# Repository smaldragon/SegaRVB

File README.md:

# Sega R.V.B. Clone Board

This is a clone of the "Adapteur R.V.B.", used by the french market Master System II for video output, based on the schematics avaliable at [SMSPower.org](https://www.smspower.org/Development/AdapteurRVB).

This board is intended to be a cheap diy option for consoles which have lost their original cable, and comes with all the quirks of the original circuit.

The wires of a custom DIN-8 AV cable should be soldered to the through hole pins in the bottom of the board to connect the board to an original console.

> Note: the non-critical 12V pin 8 signal which sets the tv to 4:3 mode has been ommitted from this board for simplification.

## Bill of Materials

The location and values of all Components are specified on the board itself.

| Component | Quantity |
|-----------|----------|
| Female PCB SCART Connector    | 1 |
| 1µF Decoupling Capacitor      | 1 |
| Generic Diode                 | 1 |
| Generic NPN Transistor        | 4 |
| 27Ω Resistor                  | 4 |
| 68Ω Resistor                  | 4 |
| 75Ω Resistor                  | 2 |
| 100Ω Resistor                 | 1 |
| 820Ω Resistor                 | 1 |
| 1kΩ Resistor                  | 3 |
| 3.3kΩ Resistor                | 3 |
| 10kΩ Resistor                 | 2 |
| 12kΩ Resistor                 | 3 |

## Files

The `kicad` folder contains the original files used to produce the board
The `gerber` folder contain zip files with the gerber files for board production

## Revisions

As of 2023-09-29, my latest board revision is **v0b**

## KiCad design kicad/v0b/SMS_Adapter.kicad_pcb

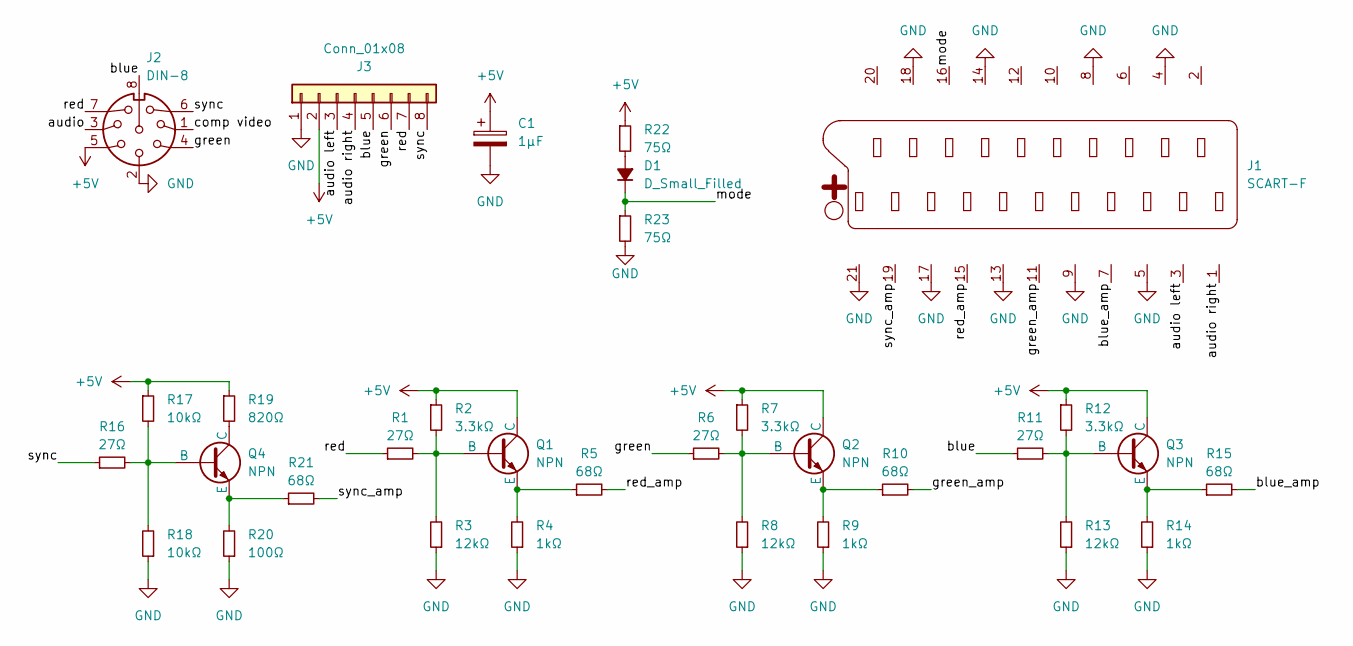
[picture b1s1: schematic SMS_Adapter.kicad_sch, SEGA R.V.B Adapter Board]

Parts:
C1: 1µF; CP_Radial_D5.0mm_P2.50mm
D1: D_Small_Filled; D_DO-34_SOD68_P7.62mm_Horizontal
J1: SCART-F; SCART
J2: DIN-8
J3: Conn_01x08; PinSocket_1x08_P2.54mm_Vertical
Q1, Q2, Q3, Q4: NPN; TO-92L_HandSolder
R1, R6, R11, R16: 27Ω; R_Axial_DIN0207_L6.3mm_D2.5mm_P7.62mm_Horizontal
R2, R7, R12: 3.3kΩ; R_Axial_DIN0207_L6.3mm_D2.5mm_P7.62mm_Horizontal
R3, R8, R13: 12kΩ; R_Axial_DIN0207_L6.3mm_D2.5mm_P7.62mm_Horizontal
R4, R9, R14: 1kΩ; R_Axial_DIN0207_L6.3mm_D2.5mm_P7.62mm_Horizontal
R5, R10, R15, R21: 68Ω; R_Axial_DIN0207_L6.3mm_D2.5mm_P7.62mm_Horizontal
R17, R18: 10kΩ; R_Axial_DIN0207_L6.3mm_D2.5mm_P7.62mm_Horizontal
R19: 820Ω; R_Axial_DIN0207_L6.3mm_D2.5mm_P7.62mm_Horizontal
R20: 100Ω; R_Axial_DIN0207_L6.3mm_D2.5mm_P7.62mm_Horizontal
R22, R23: 75Ω; R_Axial_DIN0207_L6.3mm_D2.5mm_P7.62mm_Horizontal

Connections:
+5V: C1.1, J2.5, J3.2, Q1.1 (C), Q2.1 (C), Q3.1 (C), R2.1, R7.1, R12.1, R17.1, R19.1, R22.1
/audio left: J1.3, J3.3
/audio right: J1.1, J3.4
/blue: J2.8, J3.5, R11.1
/blue_amp: J1.7, R15.2
/green: J2.4, J3.6, R6.1
/green_amp: J1.11, R10.2
/mode: D1.1 (K), J1.16, R23.1
/red: J2.7, J3.7, R1.1
/red_amp: J1.15, R5.2
/sync: J2.6, J3.8, R16.1
/sync_amp: J1.19, R21.2
GND: C1.2, J1.4, J1.5, J1.8, J1.9, J1.13, J1.14, J1.17, J1.18, J1.21, J2.2, J3.1, R3.1, R4.1, R8.1, R9.1, R13.1, R14.1, R18.1, R20.1, R23.2
unnamed: D1.2 (A), R22.2
unnamed: Q1.2 (B), R1.2, R2.2, R3.2
unnamed: Q1.3 (E), R4.2, R5.1
unnamed: Q2.2 (B), R6.2, R7.2, R8.2
unnamed: Q2.3 (E), R9.2, R10.1
unnamed: Q3.2 (B), R11.2, R12.2, R13.2
unnamed: Q3.3 (E), R14.2, R15.1
unnamed: Q4.2 (B), R16.2, R17.2, R18.2
unnamed: Q4.1 (C), R19.2
unnamed: Q4.3 (E), R20.2, R21.1

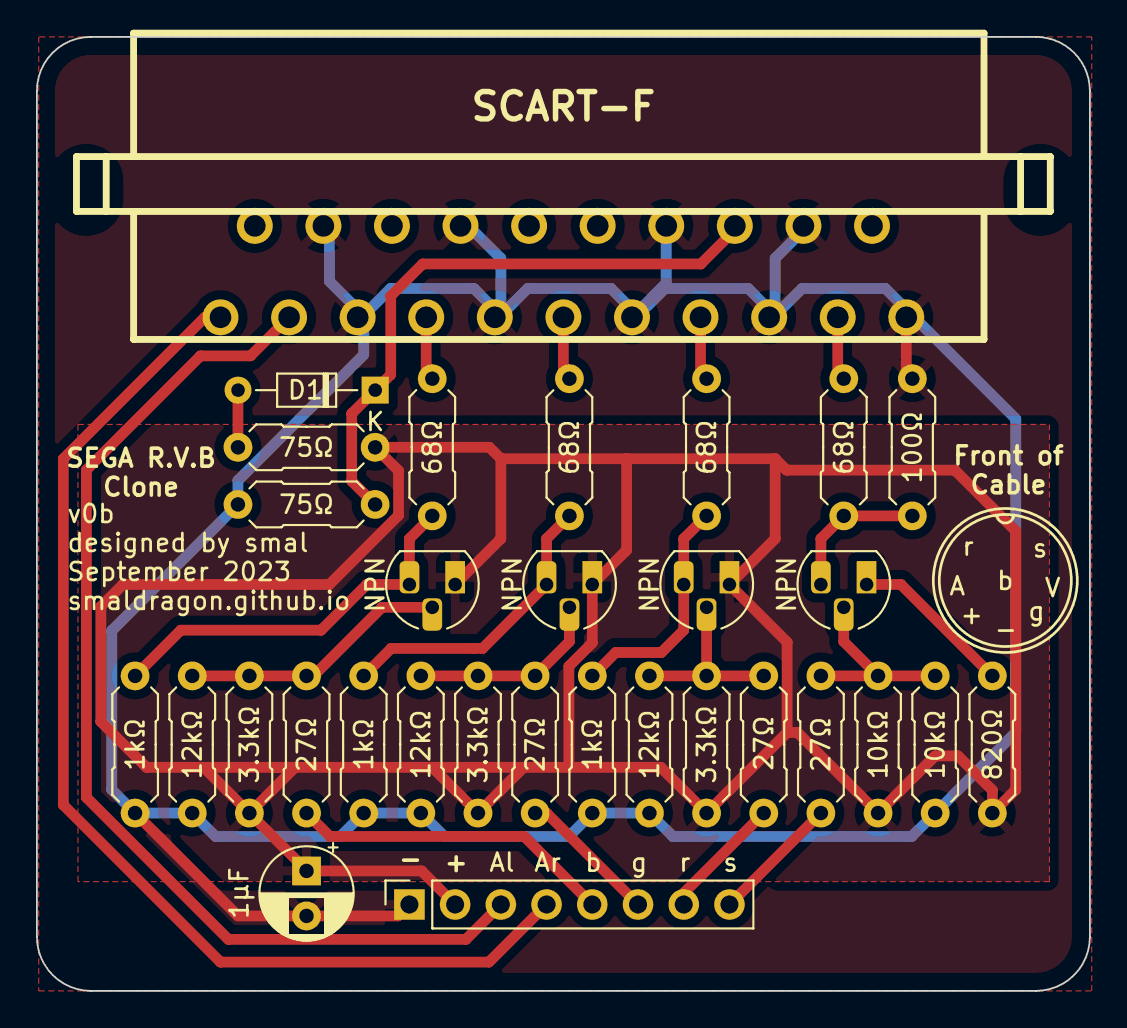
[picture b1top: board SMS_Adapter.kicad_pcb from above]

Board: 2 copper layers, 58.5 x 53.0 mm, 31 parts (0 on the bottom side), 23 nets.

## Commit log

2023-09-29 Initial file commit
2023-09-29 add circuit schematic image
